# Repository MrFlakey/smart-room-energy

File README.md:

# Smart Room Energy Management: ESP32 firmware

Author: Mohamed Khamis

A smart room that saves energy on its own. An ESP32 watches occupancy, the door, temperature, daylight and power use, then switches the lights and the "AC" (a DC fan) only when they are needed. Everything is shown live on a 3D digital twin over MQTT: [Smart-Room-Digital-Twin](https://github.com/MrFlakey/Smart-Room-Digital-Twin).

This repository holds the ESP32 firmware: the room application and an ESP-IDF driver component for every sensor and actuator. How the firmware is organised (tasks, fault detection, settings) is in [`firmware/README.md`](firmware/README.md).

## How the room behaves

- **Occupancy:** the PIR sensor detects people; the room counts as empty after 15 s without motion.
- **Door:** an ultrasonic sensor watches the door. If it stays open for about 10 s, the AC pauses and resumes when it closes.
- **AC:** the fan stands in for the AC. A rotation knob sets the target temperature, the fan speed grows with how far the room is above target, and it is always off in an empty room.
- **Lights:** two LEDs are dimmed from the ambient light sensor (daylight harvesting), only while the room is occupied.
- **Buttons:** B1 toggles the lights, B2 toggles the AC, B3 switches Auto/Manual. In Auto a press overrides the automatic control until the room is empty.
- **Energy:** a DFRobot SEN0291 wattmeter measures live power, total energy and the percentage saved against "always on".
- **Reliability:** the room runs offline on its own. A failed sensor switches off what depends on it and is reported to the twin.

## Hardware

| Part | Model |
|---|---|
| Board | ESP32 DevKit v1 |
| Motion | PIR sensor |
| Door | DFRobot SEN0307 ultrasonic sensor (URM09, analog) |
| Temperature | LM35 |
| Ambient light | analog light sensor |
| Target temperature | rotation sensor (potentiometer) |
| Power | DFRobot SEN0291 I2C wattmeter |
| Controls | 3 pushbuttons |
| Lights | 2 LEDs |
| AC | DC fan module |

The pin map is in [`firmware/main/board_pins.h`](firmware/main/board_pins.h) and the full wiring table is in [`firmware/README.md`](firmware/README.md). ESP32 pins are 3.3 V only, so the parts that send an analog signal (light sensor, knob, ultrasonic) run from 3V3.

## Drivers

Written for **ESP-IDF v6.0** using only the current IDF drivers (ADC oneshot with calibration, `i2c_master`, LEDC, GPIO, `esp_timer`).

| Component | Part |
|---|---|
| `analog_in` | shared ADC1 helper used by the analog drivers |
| `lm35` | temperature |
| `light_sensor` | ambient light |
| `rotation_sensor` | target temperature knob |
| `sen0307` | ultrasonic distance (door) |
| `pir` | motion |
| `sen0291` | I2C wattmeter |
| `button` | debounced pushbuttons with callbacks |
| `led` | dimmable LEDs |
| `fan` | PWM fan module |

Every driver works the same way: fill a config struct with its `*_DEFAULT_CONFIG(...)` macro, call `*_create()` to get a handle, then use the read/set functions. The reference for each driver is in [`firmware/README.md`](firmware/README.md) and in its folder under [`firmware/components/`](firmware/components).

## Build and flash

1. Install ESP-IDF v6.0 (for example with the ESP-IDF VS Code extension).
2. Open the `firmware` folder.
3. Set the Wi-Fi network in **menuconfig → Smart Room** (stored in the git-ignored `sdkconfig`).
4. Set the target to `esp32`, pick the board's serial port, then **Build, Flash and Monitor**.

From a terminal with ESP-IDF loaded:

```
cd firmware
idf.py set-target esp32
idf.py menuconfig
idf.py -p <PORT> flash monitor
```

## Branches

- `main`: the driver components with an empty `app_main`.
- `testing`: the room application, hardware tests and per-driver documentation.

## Network

The ESP32 talks MQTT to a local Mosquitto broker on base topic `smartroom/room1/`. The message format is defined in the twin repository's [`docs/mqtt-contract.md`](https://github.com/MrFlakey/Smart-Room-Digital-Twin/blob/main/docs/mqtt-contract.md).

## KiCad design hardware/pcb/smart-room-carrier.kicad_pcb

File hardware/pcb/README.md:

# Smart Room carrier board (KiCad)

Author: Mohamed Khamis

A 110 × 82 mm two-layer carrier board for the ESP32 DevKit V1 (30-pin) and the DFRobot Gravity modules in [docs/esp32-wiring.md](../../docs/esp32-wiring.md). The DevKit plugs into two 1×15 female headers, and every module plugs into its own 3-pin header with the pin numbers from `firmware/main/board_pins.h`.

Checked with KiCad 10.0.6: ERC 0 errors and 0 warnings, DRC 0 violations, 0 unconnected items, 0 schematic/board mismatches ([erc.rpt](erc.rpt), [drc.rpt](drc.rpt)).

## Files

| File | What it is |
|---|---|
| `smart-room-carrier.kicad_pro` | KiCad project (open this one) |
| `smart-room-carrier.kicad_sch` | Schematic |
| `smart-room-carrier.kicad_pcb` | Board, placed and routed, with a GND pour on the bottom layer |
| `SmartRoom.kicad_sym`, `SmartRoom.pretty/` | Project symbol and footprint libraries |
| `smart-room-carrier-schematic.pdf` | Schematic as PDF |
| `gerbers/`, `smart-room-carrier-gerbers.zip` | Gerber and drill files for ordering the board (upload the zip to JLCPCB, PCBWay, etc.) |
| `render-top.png`, `render-bottom.png` | 3D renders of both sides |
| `erc.rpt`, `drc.rpt` | KiCad check reports |
| `gen/` | Python scripts that generate the project (`python gen/build.py`) |
| `preview.svg` | Quick picture of the routed board |

## Connectors

Every module header is **G V S** (GND, VCC, signal), printed on the board next to the pins. With a Gravity-to-Dupont cable: black to G, red to V, green or blue to S.

| Header | Module | ESP32 pin | VCC default |
|---|---|---|---|
| J1 TEMP | DFR0023 LM35 | GPIO34 | **5V** (the LM35 needs at least 4 V) |
| J2 LIGHT | DFR0026 | GPIO35 | 3V3 |
| J3 ROT | DFR0058 | GPIO32 | 3V3 |
| J4 ULTRA | SEN0307 | GPIO33 | 3V3 |
| J5 PIR | SEN0018 | GPIO27 | 3V3 |
| J6 BTN3 A/M | DFR0029 | GPIO23 | 3V3 |
| J7 LED1 | DFR0021 | GPIO26 | 3V3 |
| J8 BTN1 LIGHT | DFR0029 | GPIO14 | 3V3 |
| J9 BTN2 AC | DFR0029 | GPIO13 | 3V3 |
| J10 FAN | DFR0411 | GPIO25 | metered 5 V (fixed) |
| J11 LED2 | DFR0021 | GPIO19 | 3V3 |
| J12 WATT I2C (− + C D) | SEN0291 data side | SCL GPIO22, SDA GPIO21 | 3V3 |
| J13 WATT IN+/IN− | SEN0291 screw terminals | – | IN+ = VIN 5 V, IN− = fan 5 V |
| J14 BAT 5V | 5 V battery (screw terminal, + and −) | – | – |

## Choosing 5 V or 3.3 V for a module

Each module (except the fan) has a 3-pin jumper header labelled **5V** and **3V3** at its ends. The middle pin is the module's VCC.

- Jumper cap on the **5V** end and the middle pin: the module runs on 5 V.
- Jumper cap on the middle pin and the **3V3** end: the module runs on 3.3 V.

Moving a module to 5 V is safe for the ESP32: every signal goes through a series resistor (1 kΩ for inputs, 220 Ω for outputs) and a BAT54S clamp to GND and 3V3, so the GPIO can't go above about 3.6 V. The wattmeter's I2C lines go through a BSS138 level shifter, so it works on either supply. Keep in mind that an analog module on 5 V can output more than 3.3 V, and readings above about 3.1 V are clipped by the ESP32's ADC.

## Power and ground

- **Fan path:** VIN (5 V) → J13 IN+ → SEN0291 → J13 IN− → fan VCC. The wattmeter therefore measures the fan. Without the wattmeter, put a jumper cap on **JP12 BYPASS**; take it off again when the wattmeter is connected, or the meter is bypassed.
- **Fan decoupling:** C5 (470 µF) and C6 (100 nF) sit next to the fan header to absorb motor current spikes.
- **Star ground:** the fan's ground (GND_FAN) is a separate net that only joins logic GND at NT1, right next to the DevKit's GND pin. Motor return current doesn't flow through the sensor and I2C ground.
- **Sensor 5 V:** the 5 V for the module jumpers (+5V_S) is filtered from VIN by ferrite bead FB1 and C7, so fan noise stays off the sensor supply.

## Running from a battery

The board runs from the DevKit's USB port, from a 5 V battery on **J14 BAT 5V**, or from both at once.

- **Which batteries:** anything that gives a steady 5 V (a power bank with bare wires, a 5 V regulator) or 4× AA NiMH (4.8 V). Don't use 4× AA alkaline (6 V when fresh): the fan and any module jumpered to 5V would get 6 V. A single Li-ion cell (3.7 V) needs a 5 V boost converter in front of J14.
- **On/off:** **JP13 BAT ON** sits between the terminal and the board. Put a jumper cap on it to run from the battery, or wire an on/off switch to its two pins.
- **Protection:** the battery reaches the 5 V rail (VIN) through D12, an SS34 Schottky diode. If the battery is connected backwards, the diode blocks it. With USB plugged in as well, the diode stops USB from charging or back-feeding the battery.
- **Voltage drop:** the diode drops about 0.3 V, so on a 5 V battery the rail sits around 4.7 V. Everything works at that, including the LM35 (needs at least 4 V). The fan runs slightly slower.
- **Run time:** the board draws roughly 100–150 mA with the fan off and a few hundred mA with the fan on. A 2000 mAh NiMH pack lasts about 10–15 hours with the fan mostly off.

## DevKit header spacing

30-pin DevKit V1 boards come with the two pin rows either 25.4 mm (1.0") or 22.86 mm (0.9") apart. The right-hand row has holes for both. Measure your board, solder the right-hand female header into the row that fits, and leave the other row empty.

## Bill of materials

| Ref | Qty | Part |
|---|---|---|
| U1 | 2 | 1×15 female header, 2.54 mm (socket for the DevKit) |
| J1–J11 | 11 | 1×03 male header, 2.54 mm |
| J12 | 1 | 1×04 male header, 2.54 mm |
| J13 | 1 | 1×02 male header, 2.54 mm |
| J14 | 1 | 2-pin screw terminal, 5.08 mm |
| JP1–JP11 | 11 | 1×03 male header + jumper cap |
| JP12, JP13 | 2 | 1×02 male header + jumper cap (JP13 can take an external switch instead) |
| R1–R11 | 11 | 0805 resistor: 1 kΩ for inputs, 220 Ω for LED1, LED2 and FAN |
| R12–R15 | 4 | 0805 resistor 4.7 kΩ (I2C pull-ups) |
| D1–D11 | 11 | BAT54S, SOT-23 |
| D12 | 1 | SS34 Schottky diode, SMA (3 A, 40 V) |
| Q1, Q2 | 2 | BSS138, SOT-23 |
| C1–C4 | 4 | 0805 10 nF (analog inputs) |
| C5 | 1 | 470 µF 10 V electrolytic, D8 mm, 3.5 mm pitch |
| C6, C9 | 2 | 0805 100 nF |
| C7, C8 | 2 | 0805 10 µF 16 V |
| FB1 | 1 | 0805 ferrite bead, 600 Ω @ 100 MHz, at least 500 mA |
| H1–H4 | 4 | M3 mounting holes |

## Regenerating

`python gen/build.py` rewrites the schematic, board, libraries and preview from `gen/design.py`. Hand edits made in KiCad are overwritten, so once you start editing the board in KiCad, stop using the script.

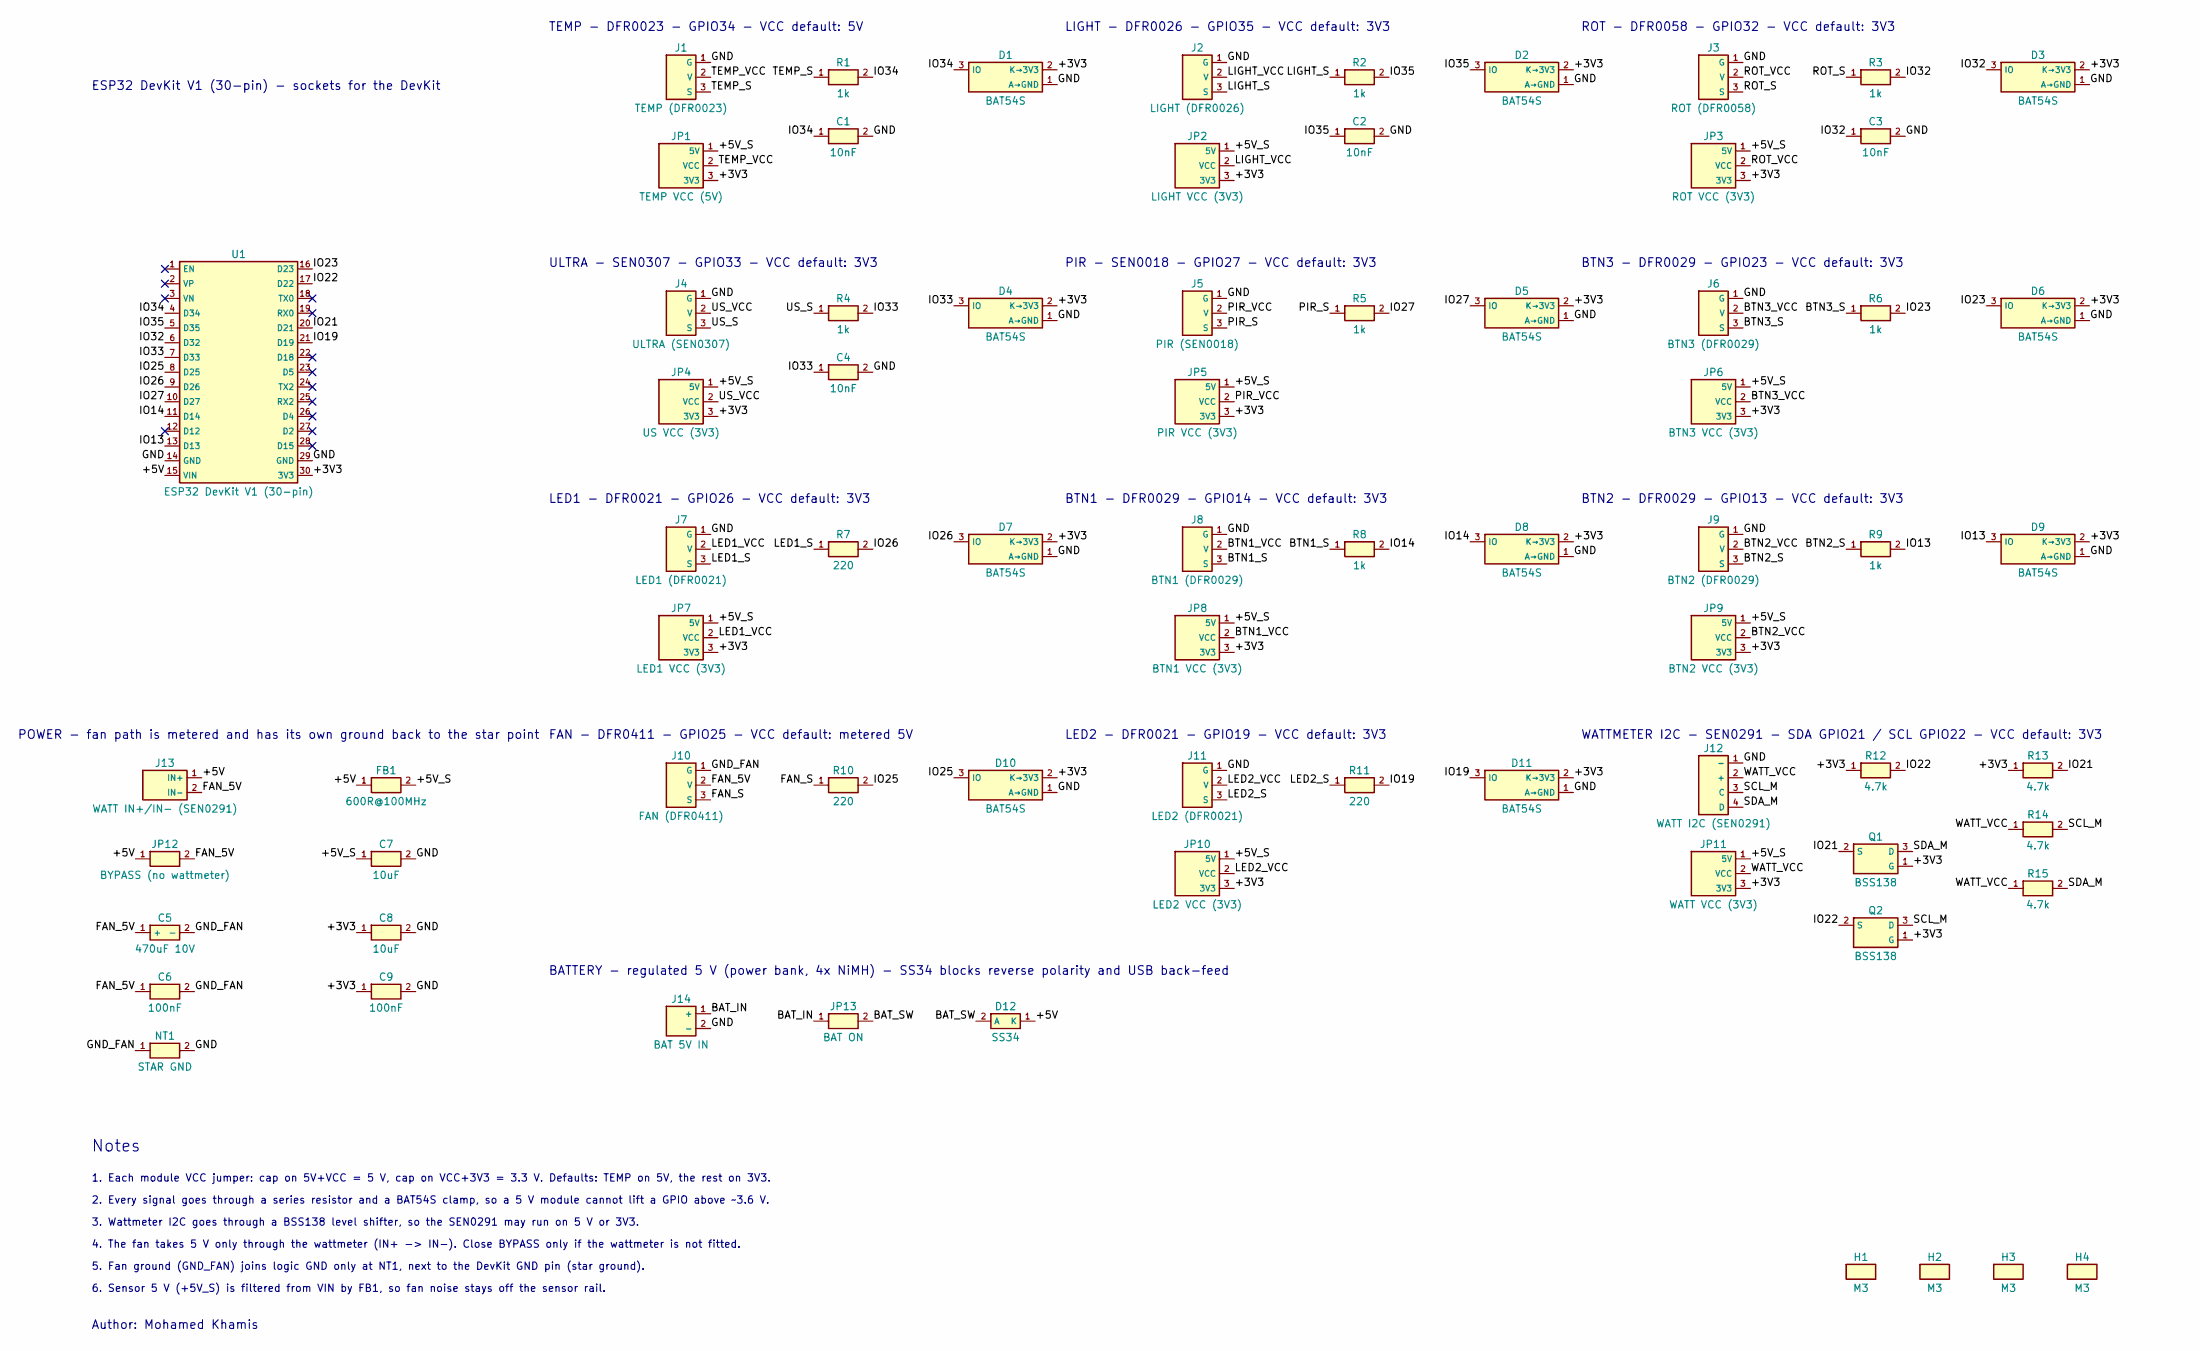
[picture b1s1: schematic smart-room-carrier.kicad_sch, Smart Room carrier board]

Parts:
C1, C2, C3, C4: 10nF; C_0805_HandSolder; Part 0805 X7R
C5: 470uF 10V; CP_Radial_D8.0mm_P3.50mm; Part Electrolytic 470uF 10V D8
C6, C9: 100nF; C_0805_HandSolder; Part 0805 X7R
C7, C8: 10uF; C_0805_HandSolder; Part 0805 X5R 16V
D1, D2, D3, D4, D5, D6, D7, D8, D9, D10, D11: BAT54S; SOT-23; Part BAT54S
D12: SS34; D_SMA; Part SS34 (3 A, 40 V Schottky)
FB1: 600R@100MHz; L_0805_HandSolder; Part 0805 ferrite bead, >=500 mA
H1, H2, H3, H4: M3; MountingHole_3.2mm_M3
J1: TEMP (DFR0023); PinHeader_1x03_P2.54mm; Part 1x03 male header 2.54 mm
J2: LIGHT (DFR0026); PinHeader_1x03_P2.54mm; Part 1x03 male header 2.54 mm
J3: ROT (DFR0058); PinHeader_1x03_P2.54mm; Part 1x03 male header 2.54 mm
J4: ULTRA (SEN0307); PinHeader_1x03_P2.54mm; Part 1x03 male header 2.54 mm
J5: PIR (SEN0018); PinHeader_1x03_P2.54mm; Part 1x03 male header 2.54 mm
J6: BTN3 (DFR0029); PinHeader_1x03_P2.54mm; Part 1x03 male header 2.54 mm
J7: LED1 (DFR0021); PinHeader_1x03_P2.54mm; Part 1x03 male header 2.54 mm
J8: BTN1 (DFR0029); PinHeader_1x03_P2.54mm; Part 1x03 male header 2.54 mm
J9: BTN2 (DFR0029); PinHeader_1x03_P2.54mm; Part 1x03 male header 2.54 mm
J10: FAN (DFR0411); PinHeader_1x03_P2.54mm; Part 1x03 male header 2.54 mm
J11: LED2 (DFR0021); PinHeader_1x03_P2.54mm; Part 1x03 male header 2.54 mm
J12: WATT I2C (SEN0291); PinHeader_1x04_P2.54mm; Part 1x04 male header 2.54 mm
J13: WATT IN+/IN- (SEN0291); PinHeader_1x02_P2.54mm; Part 1x02 male header 2.54 mm
J14: BAT 5V IN; TerminalBlock_1x02_P5.08mm; Part 2-pin screw terminal 5.08 mm
JP1: TEMP VCC (5V); PinHeader_1x03_P2.54mm; Part 1x03 male header + jumper cap
JP2: LIGHT VCC (3V3); PinHeader_1x03_P2.54mm; Part 1x03 male header + jumper cap
JP3: ROT VCC (3V3); PinHeader_1x03_P2.54mm; Part 1x03 male header + jumper cap
JP4: US VCC (3V3); PinHeader_1x03_P2.54mm; Part 1x03 male header + jumper cap
JP5: PIR VCC (3V3); PinHeader_1x03_P2.54mm; Part 1x03 male header + jumper cap
JP6: BTN3 VCC (3V3); PinHeader_1x03_P2.54mm; Part 1x03 male header + jumper cap
JP7: LED1 VCC (3V3); PinHeader_1x03_P2.54mm; Part 1x03 male header + jumper cap
JP8: BTN1 VCC (3V3); PinHeader_1x03_P2.54mm; Part 1x03 male header + jumper cap
JP9: BTN2 VCC (3V3); PinHeader_1x03_P2.54mm; Part 1x03 male header + jumper cap
JP10: LED2 VCC (3V3); PinHeader_1x03_P2.54mm; Part 1x03 male header + jumper cap
JP11: WATT VCC (3V3); PinHeader_1x03_P2.54mm; Part 1x03 male header + jumper cap
JP12: BYPASS (no wattmeter); PinHeader_1x02_P2.54mm; Part 1x02 male header + jumper cap
JP13: BAT ON; PinHeader_1x02_P2.54mm; Part 1x02 male header + jumper cap (or exter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
NT1: STAR GND; NetTie_2_Pad1.0mm; Part (copper only)
Q1, Q2: BSS138; SOT-23; Part BSS138
R1, R2, R3, R4, R5, R6, R8, R9: 1k; R_0805_HandSolder; Part 0805 1%
R7, R10, R11: 220; R_0805_HandSolder; Part 0805 1%
R12, R13, R14, R15: 4.7k; R_0805_HandSolder; Part 0805 1%
U1: ESP32 DevKit V1 (30-pin); ESP32_DevKitV1_30pin_Socket; Part 2x 1x15 female header, 2.54 mm

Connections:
/+3V3: C8.1, C9.1, D1.2 (K→3V3), D2.2 (K→3V3), D3.2 (K→3V3), D4.2 (K→3V3), D5.2 (K→3V3), D6.2 (K→3V3), D7.2 (K→3V3), D8.2 (K→3V3), D9.2 (K→3V3), D10.2 (K→3V3), D11.2 (K→3V3), JP1.3 (3V3), JP2.3 (3V3), JP3.3 (3V3), JP4.3 (3V3), JP5.3 (3V3), JP6.3 (3V3), JP7.3 (3V3), JP8.3 (3V3), JP9.3 (3V3), JP10.3 (3V3), JP11.3 (3V3), Q1.1 (G), Q2.1 (G), R12.1, R13.1, U1.30 (3V3)
/+5V: D12.1 (K), FB1.1, J13.1 (IN+), JP12.1, U1.15 (VIN)
/+5V_S: C7.1, FB1.2, JP1.1 (5V), JP2.1 (5V), JP3.1 (5V), JP4.1 (5V), JP5.1 (5V), JP6.1 (5V), JP7.1 (5V), JP8.1 (5V), JP9.1 (5V), JP10.1 (5V), JP11.1 (5V)
/BAT_IN: J14.1 (+), JP13.1
/BAT_SW: D12.2 (A), JP13.2
/BTN1_S: J8.3 (S), R8.1
/BTN1_VCC: J8.2 (V), JP8.2 (VCC)
/BTN2_S: J9.3 (S), R9.1
/BTN2_VCC: J9.2 (V), JP9.2 (VCC)
/BTN3_S: J6.3 (S), R6.1
/BTN3_VCC: J6.2 (V), JP6.2 (VCC)
/FAN_5V: C5.1 (+), C6.1, J10.2 (V), J13.2 (IN-), JP12.2
/FAN_S: J10.3 (S), R10.1
/GND: C1.2, C2.2, C3.2, C4.2, C7.2, C8.2, C9.2, D1.1 (A→GND), D2.1 (A→GND), D3.1 (A→GND), D4.1 (A→GND), D5.1 (A→GND), D6.1 (A→GND), D7.1 (A→GND), D8.1 (A→GND), D9.1 (A→GND), D10.1 (A→GND), D11.1 (A→GND), J1.1 (G), J2.1 (G), J3.1 (G), J4.1 (G), J5.1 (G), J6.1 (G), J7.1 (G), J8.1 (G), J9.1 (G), J11.1 (G), J12.1 (-), J14.2 (-), NT1.2, U1.14 (GND), U1.29 (GND)
/GND_FAN: C5.2 (-), C6.2, J10.1 (G), NT1.1
/IO13: D9.3 (IO), R9.2, U1.13 (D13)
/IO14: D8.3 (IO), R8.2, U1.11 (D14)
/IO19: D11.3 (IO), R11.2, U1.21 (D19)
/IO21: Q1.2 (S), R13.2, U1.20 (D21)
/IO22: Q2.2 (S), R12.2, U1.17 (D22)
/IO23: D6.3 (IO), R6.2, U1.16 (D23)
/IO25: D10.3 (IO), R10.2, U1.8 (D25)
/IO26: D7.3 (IO), R7.2, U1.9 (D26)
/IO27: D5.3 (IO), R5.2, U1.10 (D27)
/IO32: C3.1, D3.3 (IO), R3.2, U1.6 (D32)
/IO33: C4.1, D4.3 (IO), R4.2, U1.7 (D33)
/IO34: C1.1, D1.3 (IO), R1.2, U1.4 (D34)
/IO35: C2.1, D2.3 (IO), R2.2, U1.5 (D35)
/LED1_S: J7.3 (S), R7.1
/LED1_VCC: J7.2 (V), JP7.2 (VCC)
/LED2_S: J11.3 (S), R11.1
/LED2_VCC: J11.2 (V), JP10.2 (VCC)
/LIGHT_S: J2.3 (S), R2.1
/LIGHT_VCC: J2.2 (V), JP2.2 (VCC)
/PIR_S: J5.3 (S), R5.1
/PIR_VCC: J5.2 (V), JP5.2 (VCC)
/ROT_S: J3.3 (S), R3.1
/ROT_VCC: J3.2 (V), JP3.2 (VCC)
/SCL_M: J12.3 (C), Q2.3 (D), R14.2
/SDA_M: J12.4 (D), Q1.3 (D), R15.2
/TEMP_S: J1.3 (S), R1.1
/TEMP_VCC: J1.2 (V), JP1.2 (VCC)
/US_S: J4.3 (S), R4.1
/US_VCC: J4.2 (V), JP4.2 (VCC)
/WATT_VCC: J12.2 (+), JP11.2 (VCC), R14.1, R15.1

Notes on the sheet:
TEMP - DFR0023 - GPIO34 - VCC default: 5V
LIGHT - DFR0026 - GPIO35 - VCC default: 3V3
ROT - DFR0058 - GPIO32 - VCC default: 3V3
ULTRA - SEN0307 - GPIO33 - VCC default: 3V3
PIR - SEN0018 - GPIO27 - VCC default: 3V3
BTN3 - DFR0029 - GPIO23 - VCC default: 3V3
LED1 - DFR0021 - GPIO26 - VCC default: 3V3
BTN1 - DFR0029 - GPIO14 - VCC default: 3V3
BTN2 - DFR0029 - GPIO13 - VCC default: 3V3
FAN - DFR0411 - GPIO25 - VCC default: metered 5V
LED2 - DFR0021 - GPIO19 - VCC default: 3V3
WATTMETER I2C - SEN0291 - SDA GPIO21 / SCL GPIO22 - VCC default: 3V3
POWER - fan path is metered and has its own ground back to the star point
BATTERY - regulated 5 V (power bank, 4x NiMH) - SS34 blocks reverse polarity and USB back-feed
ESP32 DevKit V1 (30-pin) - sockets for the DevKit
Notes
1. Each module VCC jumper: cap on 5V+VCC = 5 V, cap on VCC+3V3 = 3.3 V. Defaults: TEMP on 5V, the rest on 3V3.
2. Every signal goes through a series resistor and a BAT54S clamp, so a 5 V module cannot lift a GPIO above ~3.6 V.
3. Wattmeter I2C goes through a BSS138 level shifter, so the SEN0291 may run on 5 V or 3V3.
4. The fan takes 5 V only through the wattmeter (IN+ -> IN-). Close BYPASS only if the wattmeter is not fitted.
5. Fan ground (GND_FAN) joins logic GND only at NT1, next to the DevKit GND pin (star ground).
6. Sensor 5 V (+5V_S) is filtered from VIN by FB1, so fan noise stays off the sensor rail.
Author: Mohamed Khamis

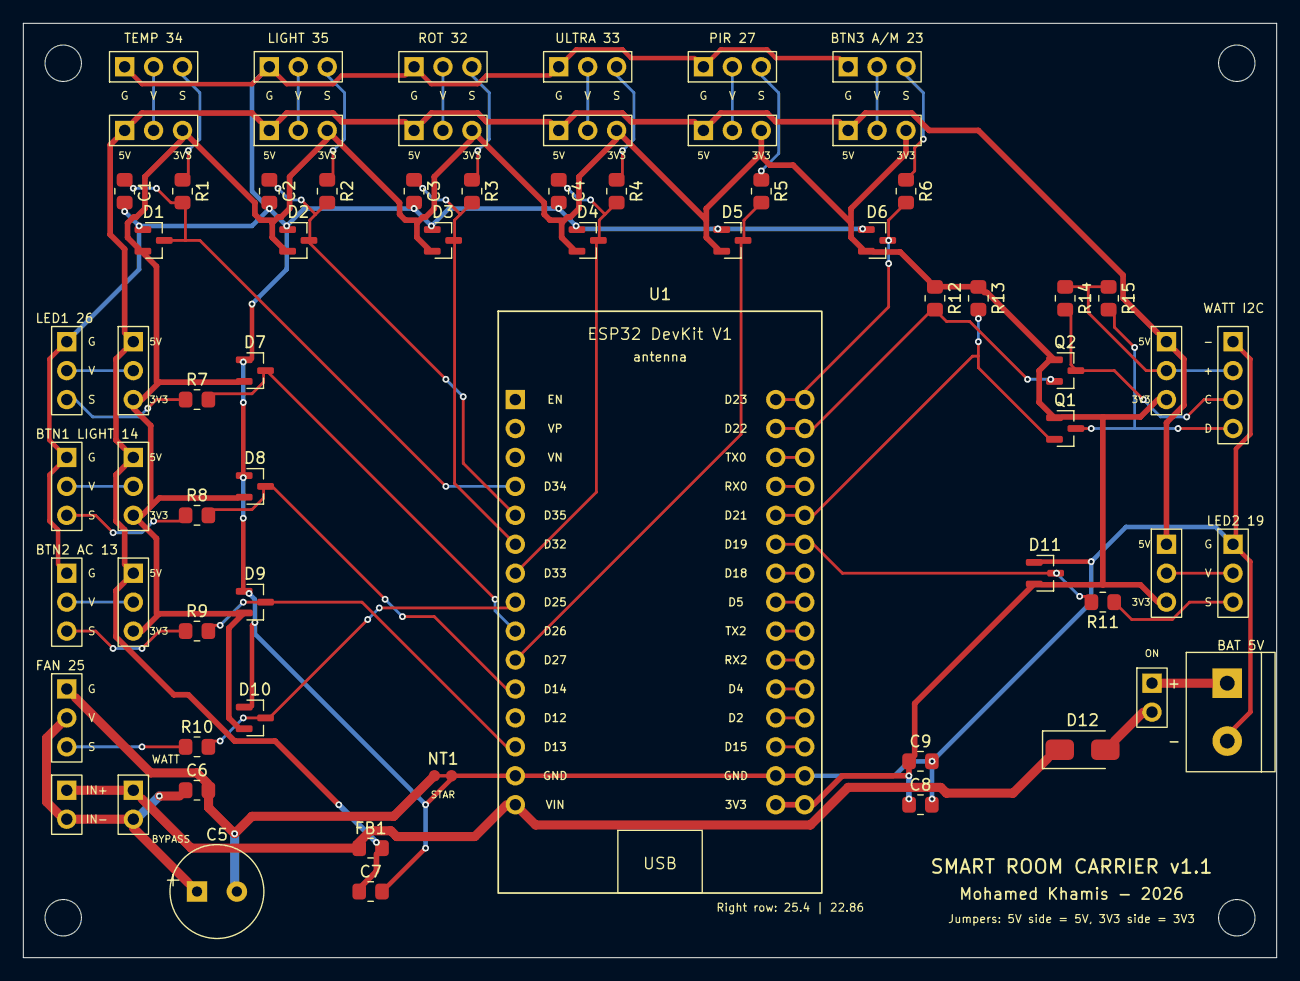
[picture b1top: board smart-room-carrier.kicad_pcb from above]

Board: 2 copper layers, 110.0 x 82.0 mm, 72 parts (0 on the bottom side), 45 nets.
